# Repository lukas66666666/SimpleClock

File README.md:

# SimpleClock
A simple clock that will hopefully wake me up.

## Features
- It displays the current time
- Set a custom alarm
## Design
### CAD
I used OnShape to design the case for the alarm clock.
### PCB
For the PCB I used KiCad.

Schematic

Finished PCB

## Firmware
The firmware is written in C++ using ArduinoIDE.
## Parts list
- 1x Seeed XIAO ESP32C3
- 3x Keyboard Switches
- 3x Keycaps
- 1x 2.25in TFT Screen
- 1x 3.3V Piezo Buzzer
- 4x M3x5x4 Heatset Inserts
- 4x M3x16mm Screws
- 3d printed case
- custom PCB
## AI
I used Claude to help me with coding the firmware and debugging.

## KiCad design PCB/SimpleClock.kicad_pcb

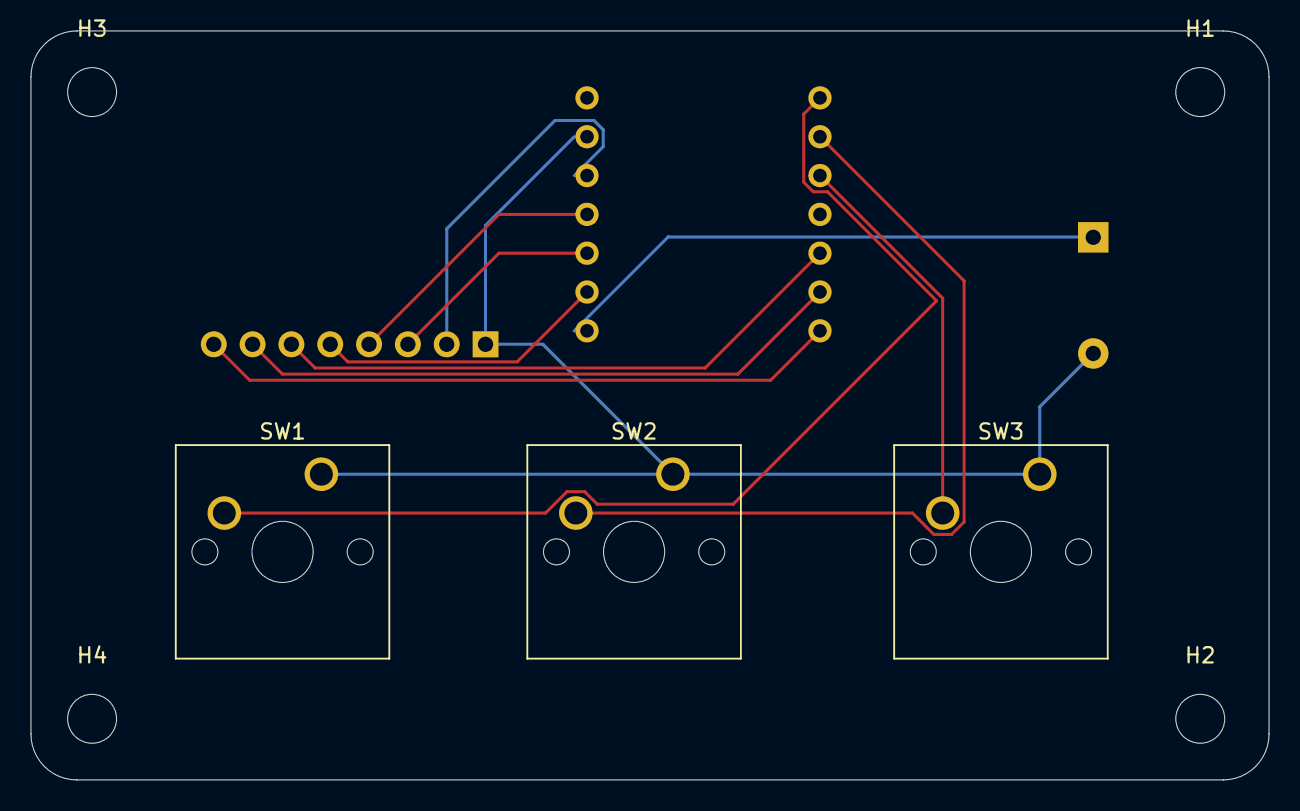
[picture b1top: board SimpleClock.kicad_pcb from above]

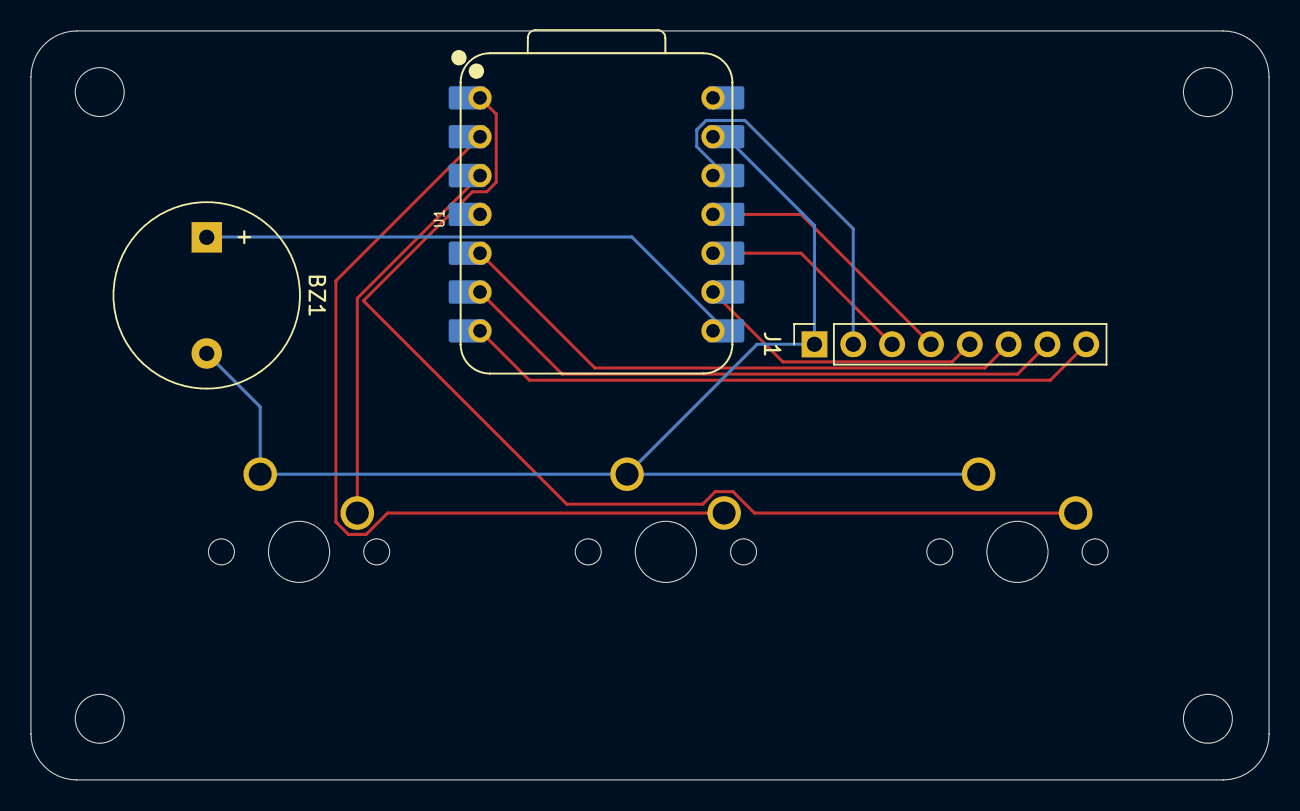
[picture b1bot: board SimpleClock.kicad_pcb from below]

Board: 2 copper layers, 81.0 x 49.0 mm, 10 parts (3 on the bottom side), 12 nets.

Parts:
BZ1: Buzzer; Buzzer_12x9.5RM7.6
H1, H2, H3, H4: MountingHole; MountingHole_3.2mm_M3
J1: Conn_01x08_Pin; PinSocket_1x08_P2.54mm_Vertical
SW1, SW2, SW3: SW_Push; SW_Cherry_MX_1.00u_PCB
U1: XIAO-ESP32-C3-SMD; XIAO-ESP32-C3-DIP

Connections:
+3.3V: J1.2, U1.12 (3V3_OUT)
/BL: J1.8, U1.7 (D6)
/CS: J1.7, U1.6 (D5)
/DC: J1.6, U1.5 (D4)
/RST: J1.5, U1.9 (D8)
/SCL: J1.3, U1.10 (D9/BOOT)
/SDA: J1.4, U1.11 (D10)
GND: BZ1.2 (-), J1.1, SW1.1, SW2.1, SW3.1, U1.13 (GND)
unnamed: BZ1.1 (+), U1.8 (D7)
unnamed: SW1.2, U1.1 (D0)
unnamed: SW2.2, U1.2 (D1)
unnamed: SW3.2, U1.3 (D2)
